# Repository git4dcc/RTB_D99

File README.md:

# RTB_D99

## This is a [opendcc](https://forum.opendcc.de/viewtopic.php?t=10443) forum project
The D99 is an advanced, open-source decoder core (AVR64DA48) designed for serious modelers. It provides individual, high-density control for up to 32 LEDs and 4 auxiliary ports. More than just control, this core is engineered for ultimate reliability:
- **Flicker-Free Power:** Includes charging logic for external Polymer or Supercapacitors for robust power backup.
- **Real-Time Diagnostics:** Harness the power of Railcom DYN to transmit vital data, including Quality of Service (QoS), track voltage, and temperature, back to your central station.
- **DIY High-Density:** Fully open-source KiCad design (4-layer PCB) ready for reflow assembly.
- **WS28xx bus**: Can drive up to 32 LEDs on a WS28xx serial bus

LED base carrier
- [Example-1: HO Roco #44741 coach](ledbase/Roco_44741)

<br>

<details>
<summary>User Guides</summary>

- User Guide - DE
- [User Guide - EN](https://rtb4dcc.de/rtb_decoder_reference_en/)

</details>

<br>

## Decoder features
- **DCC**
  - DCC-A automatic logon
  - DCC-R protocol extension
  - Service Mode Programming
- **Railcom**
  - Channel 1/2
  - POM, xPOM
  - DYN: QoS, Track-Voltage, Scap-Voltage, Temp, Ambient light
- **AUX ports**
  - 4 dimmable AUX ports (3.3V logic level)
  - AUX ports my be used for Servo
- **LED ports**
  - designed for
    - SR: 74HC595 shift registers
    - WS: WS2811 neo pixel
  - up to 32 individual LEDs using either SR or WS
- SUSI 3.3V
- 2.8V SCAP (optional, external to PCB)
- 16V Polymer Caps (optional, external to PCB)
- Inrush limited
- max track voltage 36V
- CPU heartbeat LED
- ambient light sensor (optional)
- fast firmware update on main tracks via DCC-R

# Hardware
The current PCB layout uses SMD footprints with 0.4mm pitch and mainly 0402 parts. Reflow soldering is mandatory.
The layout has been optimized to automatic PCB assembly.

| top | bottom |
| --- | --- |
|  |  |

## PCB
- 4-layer PCB, FR4, 28 x 15 x 0.8mm
- CPU: AVR64DA48

<details>
<summary>Details</summary>

<br>

<br><br>

| pin | label | direction | description |
| --- | --- | --- | --- |
| 1 | DCC-b | input | DCC signal from track |
| 3 | DCC-1 | input | DCC signal from track |
| 5 | GND | output | Decoder ground signal (after rectifier) |
| 7 | AUX-4 | output | Logic level auxiliary port (3.3V) |
| 9 | AUX-3 | output | Logic level auxiliary port (3.3V) |
| 11 | AUX-2 | output | Logic level auxiliary port (3.3V) |
| 13 | AUX-1 | output | Logic level auxiliary port (3.3V) |
| 15 | GND | output | same as pin 5 |
| 17 | VTRK | output | (+) Track voltage after rectifier (goes up to 25V) |
| 19 | NCAP | output | (+) Connect to external polymer capacitors (cap must tolerate 16V) |
| 2 | 3V3 | output | (+) Decoder CPU voltage (3.3V) |
| 4 | SUSI_clk | output | SUSI clock signal (3.3V) |
| 6 | SUSI_dat | output | SUSI data signal (3.3V) |
| 8 | uOpto | input | Connects an optional ambient light sensor |
| 10 | UPDI | in/out | CPU programming port |
| 12 | LED.oe | output | Connect to HC595 shift register output enable pin |
| 14 | LED.stcp | output | Connect to HC595 shift register staging clock pin |
| 16 | LED.ds | output | Connect to HC595 shift register data pin |
| 18 | LED.ds | output | Connect to HC595 shift register shift clock pin |
| 20 | SCAP | output | (+) Connect to external supercap (cap must tolerate 2.8V) |

</details>

## Kicad
[Schematic](doc/D99_schematic.pdf) | [Layout](doc/D99_layout.pdf) | [Gerber](gerber)

<details>
<summary>Dependency</summary>
<br>

:yellow_circle: Requires my Kicad project library [RTB_SamacSys](/../../../../git4dcc/RTB_SamacSys) in the same directory tree.

</details>

## Firmware
Filename structure: { **pcb** }{ **code** }{ **version** }.hex

Example: **D99F0001**.hex

|   | Description |
| --- | --- |
| **pcb** | Name of matching hardware (**D99**) |
| **code** | Type of code contained (**R**=rom, **B**=bootloader, **F**=flash, **U**=bld update, **P**=UPDI factory code) |
| **version** | Release version (**####**) |

[Firmware files](firmware)

## UPDI / Fuses
The fuse settings as well as the P-code (D99Pxxxx.hex) has to be installed by using UPDI.<br>

| Fuses Setting |
| --- |
||

# Images

# YouTube
See the D99 decoder core prototype in action piggyback on a LED test carrier.<br><br>

This project is intended for hobby use only and is distributed in accordance with the Apache License 2.0 agreement.

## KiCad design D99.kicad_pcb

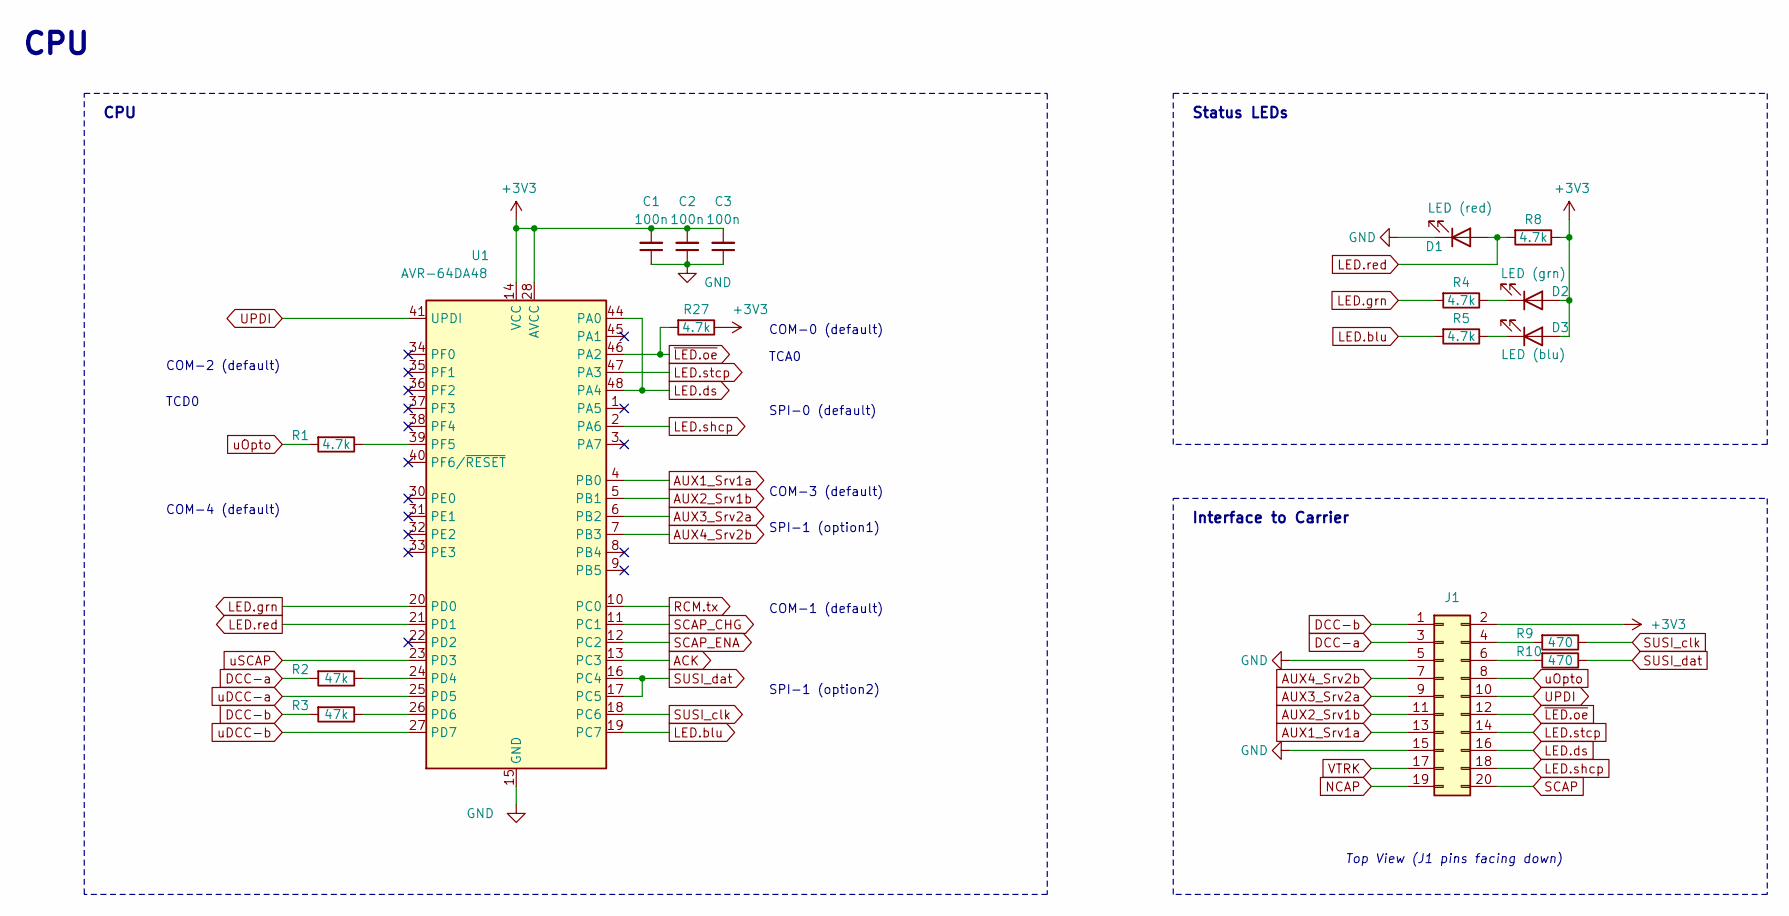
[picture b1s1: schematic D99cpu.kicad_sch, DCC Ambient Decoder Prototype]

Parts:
C1, C2, C3: 100n; C_0402_1005Metric; LCSC Part # C1525
D1: LED (red); LED_0603_1608Metric
D2: LED (grn); LED_0603_1608Metric
D3: LED (blu); LED_0603_1608Metric
J1: Conn_02x10_Counter_Clockwise; PinHeader_2x10_P1.27mm_Vertical
R1, R27: 4.7k; R_0402_1005Metric; LCSC Part # C25900
R2, R3: 47k; R_0402_1005Metric; LCSC Part # C25792
R4, R5, R8: 4.7k; R_0603_1608Metric; LCSC Part # C23162
R9, R10: 470; R_0402_1005Metric; LCSC Part # C25117
U1: AVR-64DA48; UQFN-48-1EP_6x6mm_P0.4mm_EP4.62x4.62mm; LCSC Part # C3227399

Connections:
+3V3: C1.2, C2.2, C3.2, D2.2 (A), D3.2 (A), J1.2, R8.1, R27.1, U1.14 (VCC), U1.28 (AVCC), U1.42 (VCC); also elsewhere on the board
ACK: U1.13 (PC3); also elsewhere on the board
AUX1_Srv1a: J1.13, U1.4 (PB0)
AUX2_Srv1b: J1.11, U1.5 (PB1)
AUX3_Srv2a: J1.9, U1.6 (PB2)
AUX4_Srv2b: J1.7, U1.7 (PB3)
DCC-a: J1.3, R2.2; also elsewhere on the board
DCC-b: J1.1, R3.2; also elsewhere on the board
GND: C1.1, C2.1, C3.1, D1.1 (K), J1.5, J1.15, U1.15 (GND), U1.29 (GND), U1.43 (GND), U1.49 (GND); also elsewhere on the board
LED.blu: R5.2, U1.19 (PC7)
LED.ds: J1.16, U1.44 (PA0), U1.48 (PA4)
LED.grn: R4.2, U1.20 (PD0)
LED.red: D1.2 (A), R8.2, U1.21 (PD1)
LED.shcp: J1.18, U1.2 (PA6)
LED.stcp: J1.14, U1.47 (PA3)
NCAP: J1.19; also elsewhere on the board
unnamed: D2.1 (K), R4.1
unnamed: D3.1 (K), R5.1
unnamed: J1.4, R9.2
unnamed: J1.6, R10.2
unnamed: R2.1, U1.24 (PD4)
unnamed: R3.1, U1.26 (PD6)
unnamed: R1.1, U1.39 (PF5)
RCM.tx: U1.10 (PC0); also elsewhere on the board
SCAP: J1.20, U1.23 (PD3); also elsewhere on the board
SCAP_CHG: U1.11 (PC1); also elsewhere on the board
SCAP_ENA: U1.12 (PC2); also elsewhere on the board
SUSI_clk: R9.1, U1.18 (PC6)
SUSI_dat: R10.1, U1.16 (PC4), U1.17 (PC5)
UPDI: J1.10, U1.41 (UPDI)
VTRK: J1.17; also elsewhere on the board
uDCC-a: U1.25 (PD5); also elsewhere on the board
uDCC-b: U1.27 (PD7); also elsewhere on the board
uOpto: J1.8, R1.2
~LED.oe: J1.12, R27.2, U1.46 (PA2)

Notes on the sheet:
SPI-0 (default)
TCD0
SPI-1 (option1)
Interface to Carrier
Top View (J1 pins facing down)
COM-4 (default)
CPU
COM-3 (default)
Status LEDs
SPI-1 (option2)
COM-1 (default)
COM-0 (default)
COM-2 (default)
TCA0

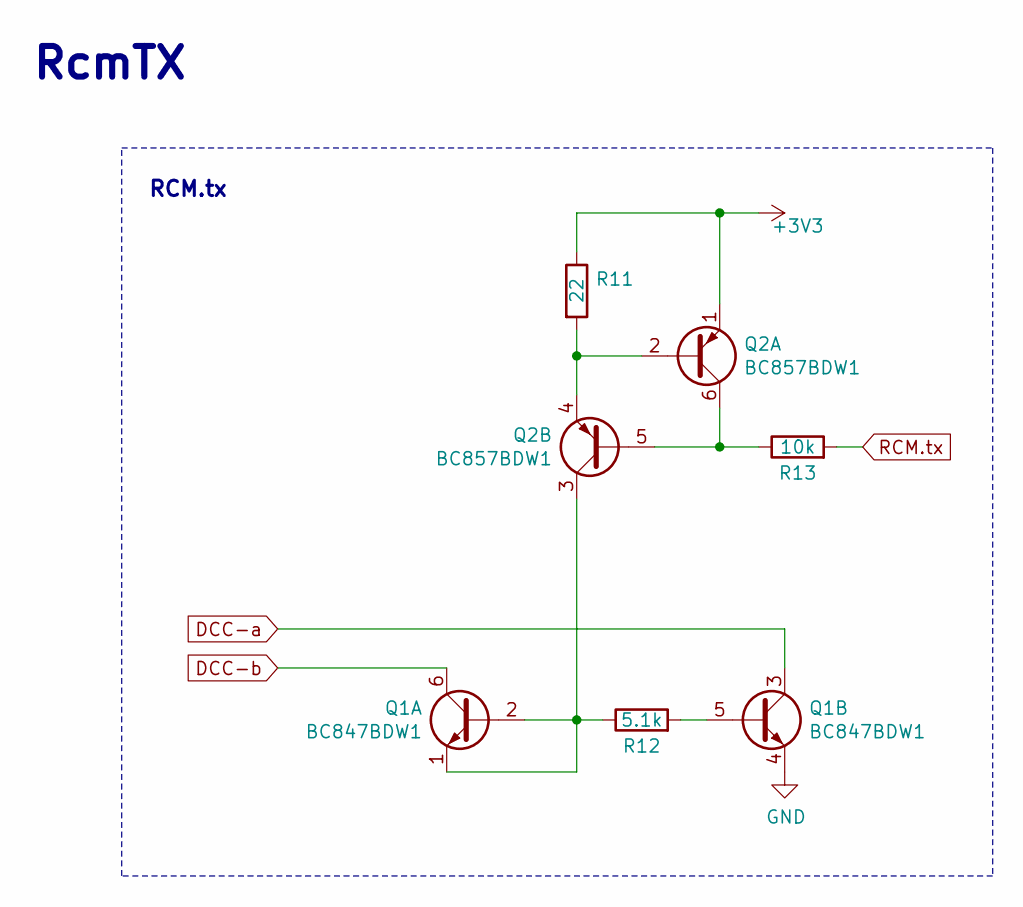
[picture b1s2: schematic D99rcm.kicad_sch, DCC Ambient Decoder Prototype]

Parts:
Q1: BC847BDW1; SOT-363_SC-70-6; LCSC Part # C82368
Q2: BC857BDW1; SOT-363_SC-70-6; LCSC Part # C154783
R11: 22; R_0402_1005Metric; LCSC Part # C25092
R12: 5.1k; R_0402_1005Metric; LCSC Part # C25905
R13: 10k; R_0402_1005Metric; LCSC Part # C25744

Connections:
+3V3: Q2.1 (E1), R11.1; also elsewhere on the board
DCC-a: Q1.3 (C2); also elsewhere on the board
DCC-b: Q1.6 (C1); also elsewhere on the board
GND: Q1.4 (E2); also elsewhere on the board
unnamed: Q1.1 (E1), Q1.2 (B1), Q2.3 (C2), R12.1
unnamed: Q1.5 (B2), R12.2
unnamed: Q2.2 (B1), Q2.4 (E2), R11.2
unnamed: Q2.5 (B2), Q2.6 (C1), R13.1
RCM.tx: R13.2; also elsewhere on the board

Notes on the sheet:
RcmTX
RCM.tx

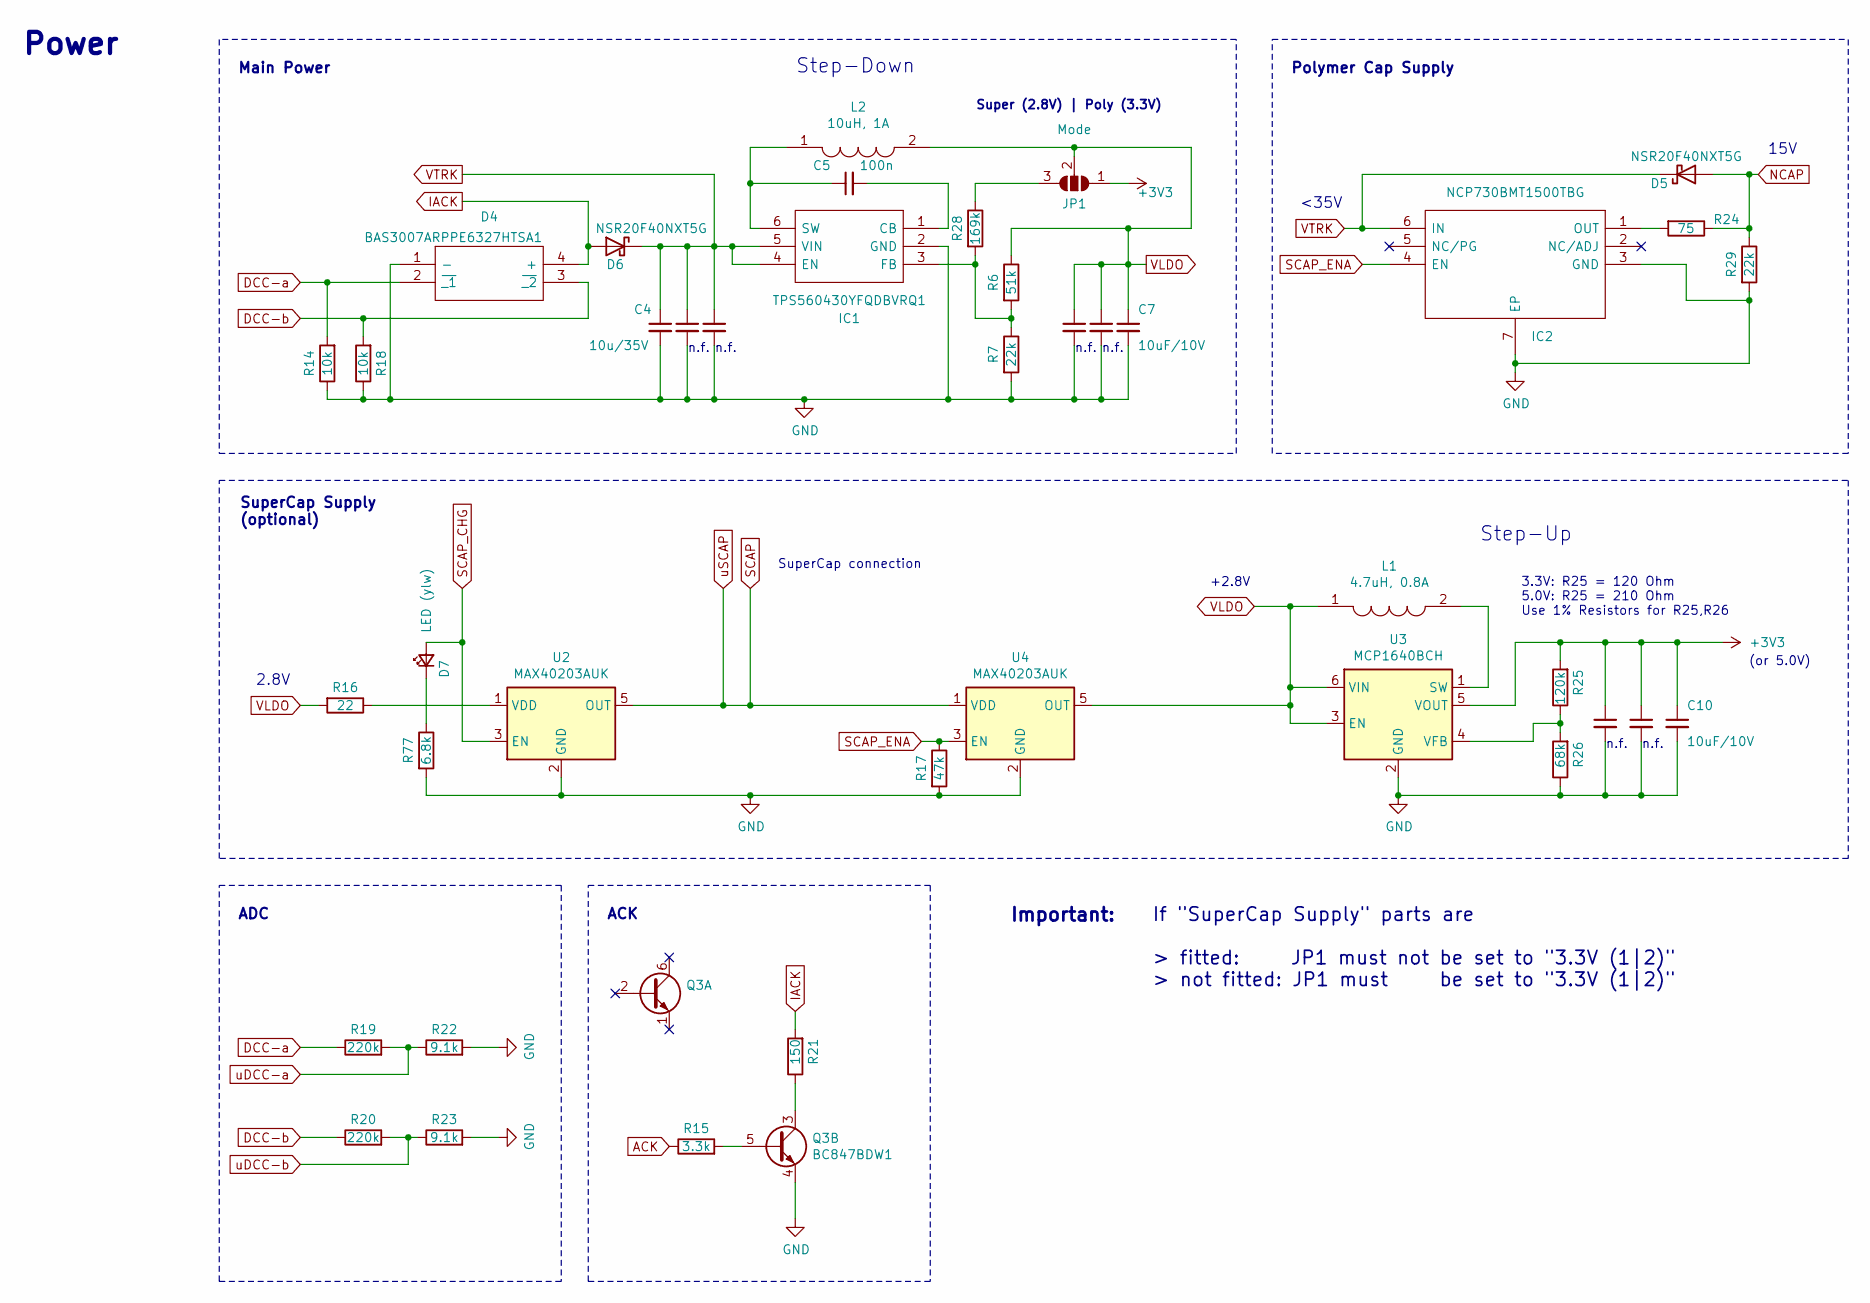
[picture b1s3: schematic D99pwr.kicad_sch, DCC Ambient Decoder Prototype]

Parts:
C4, C12, C13: 10u/35V; C_0603_1608Metric; LCSC Part # C194427
C5: 100n; C_0402_1005Metric; LCSC Part # C307331
C6, C7, C8, C9, C10, C11: 10uF/10V; C_0603_1608Metric; LCSC Part # C19702
D4: BAS3007ARPPE6327HTSA1; BF998215; LCSC Part # C6430958
D5, D6: NSR20F40NXT5G; LCSC Part # C153761
D7: LED (ylw); LED_0603_1608Metric
IC1: TPS560430YFQDBVRQ1; SOT95P280X145-6N; LCSC Part # C1849549
IC2: NCP730BMT1500TBG; SON65P200X200X80-7N; LCSC Part # C892817
JP1: Mode; SolderJumper-3_P1.3mm_Open_Pad1.0x1.5mm
L1: 4.7uH, 0.8A; WE-TPC_282892; LCSC Part # C2649333
L2: 10uH, 1A; WE-TPC_282892; LCSC Part # C2045611
Q3: BC847BDW1; SOT-363_SC-70-6; LCSC Part # C82368
R6: 51k; R_0402_1005Metric; LCSC Part # C25794
R7, R29: 22k; R_0402_1005Metric; LCSC Part # C25768
R14, R18: 10k; R_0402_1005Metric; LCSC Part # C25744
R15: 3.3k; R_0402_1005Metric; LCSC Part # C25890
R16: 22; R_0402_1005Metric; LCSC Part # C25092
R17: 47k; R_0402_1005Metric; LCSC Part # C25792
R19, R20: 220k; R_0402_1005Metric; LCSC Part # C25767
R21: 150; R_0603_1608Metric; LCSC Part # C22808
R22, R23: 9.1k; R_0402_1005Metric; LCSC Part # C25926
R24: 75; R_0603_1608Metric; LCSC Part # C4275
R25: 120k; R_0402_1005Metric; LCSC Part # C25750
R26: 68k; R_0402_1005Metric; LCSC Part # C36871
R28: 169k; R_0402_1005Metric; LCSC Part # C25758
R77: 6.8k; R_0603_1608Metric; LCSC Part # C23212
U2, U4: MAX40203AUK; SOT-23-5; LCSC Part # C2653639
U3: MCP1640BCH; SOT-23-6; LCSC Part # C478087

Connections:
+3V3: C8.1, C10.1, C11.1, JP1.1 (A), R25.2, U3.5 (VOUT); also elsewhere on the board
ACK: R15.1; also elsewhere on the board
DCC-a: D4.2 (~_1), R14.2, R19.1; also elsewhere on the board
DCC-b: D4.3 (~_2), R18.2, R20.1; also elsewhere on the board
GND: C4.2, C6.2, C7.2, C8.2, C9.2, C10.2, C11.2, C12.2, C13.2, D4.1 (-), IC1.2 (GND), IC2.3 (GND), IC2.7 (EP), Q3.4 (E2), R7.2, R14.1, R17.2, R18.1, R22.2, R23.2, R26.1, R29.2, R77.2, U2.2 (GND), U3.2 (GND), U4.2 (GND); also elsewhere on the board
IACK: D4.4 (+), D6.2 (A), R21.2
NCAP: D5.2 (A), R24.1, R29.1; also elsewhere on the board
unnamed: D7.1 (K), R77.1
unnamed: C5.2, IC1.1 (CB)
unnamed: IC1.3 (FB), R6.2, R7.1, R28.2
unnamed: C5.1, IC1.6 (SW), L2.1
unnamed: IC2.1 (OUT), R24.2
unnamed: JP1.3 (B), R28.1
unnamed: Q3.5 (B2), R15.2
unnamed: Q3.3 (C2), R21.1
unnamed: R16.1, U2.1 (VDD)
unnamed: L1.2, U3.1 (SW)
unnamed: R25.1, R26.2, U3.4 (VFB)
SCAP: U2.5 (OUT), U4.1 (VDD); also elsewhere on the board
SCAP_CHG: D7.2 (A), U2.3 (EN); also elsewhere on the board
SCAP_ENA: IC2.4 (EN), R17.1, U4.3 (EN); also elsewhere on the board
VLDO: C6.1, C7.1, C9.1, JP1.2 (C), L1.1, L2.2, R6.1, R16.2, U3.3 (EN), U3.6 (VIN), U4.5 (OUT)
VTRK: C4.1, C12.1, C13.1, D5.1 (K), D6.1 (K), IC1.4 (EN), IC1.5 (VIN), IC2.6 (IN); also elsewhere on the board
uDCC-a: R19.2, R22.1; also elsewhere on the board
uDCC-b: R20.2, R23.1; also elsewhere on the board

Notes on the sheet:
Step-Up
n.f.
Polymer Cap Supply
+2.8V
Super (2.8V) | Poly (3.3V)
(or 5.0V)
ACK
Step-Down
Power
<35V
3.3V: R25 = 120 Ohm 5.0V: R25 = 210 Ohm Use 1% Resistors for R25,R26
Main Power
SuperCap connection
If "SuperCap Supply" parts are > fitted: JP1 must not be set to "3.3V (1|2)" > not fitted: JP1 must be set to "3.3V (1|2)"
SuperCap Supply (optional)
2.8V
ADC
Important:
15V

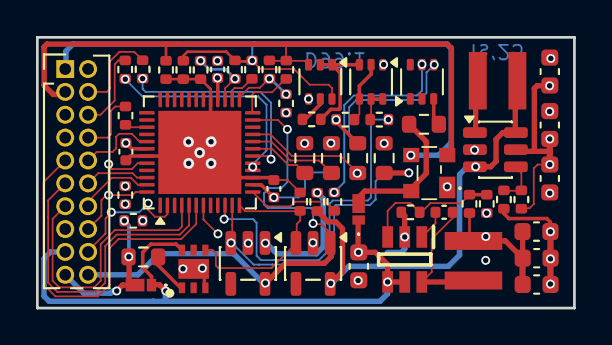
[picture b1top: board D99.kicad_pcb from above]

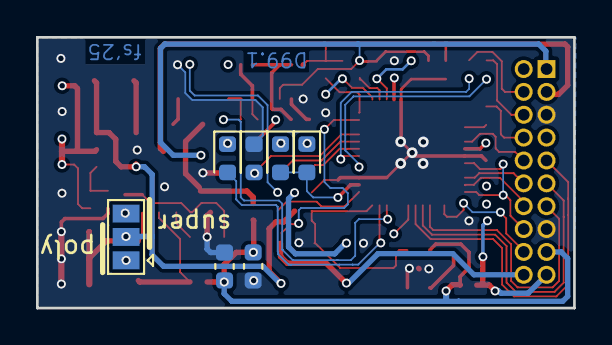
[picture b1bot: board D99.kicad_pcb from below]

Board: 4 copper layers, 29.8 x 15.0 mm, 63 parts (7 on the bottom side), 52 nets.

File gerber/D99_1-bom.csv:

Designator,Footprint,Quantity,Value,LCSC Part #
"C1, C2, C3",0402,3,100n,C1525
"C10, C11, C6, C7, C8, C9",0603,6,10uF/10V,C19702
"C12, C13, C4",0603,3,10u/35V,C194427
C5,0402,1,100n,C307331
D1,0603,1,LED (red),
D2,0603,1,LED (grn),
D3,0603,1,LED (blu),
D4,BF998215,1,BAS3007ARPPE6327HTSA1,C6430958
"D5, D6",NSR20F40NXT5G,2,NSR20F40NXT5G,C153761
D7,0603,1,LED (ylw),
IC1,SOT95P280X145-6N,1,TPS560430YFQDBVRQ1,C1849549
IC2,SON65P200X200X80-7N,1,NCP730BMT1500TBG,C892817
J1,PinHeader_2x10_P1.27mm_Vertical,1,Conn_02x10_Counter_Clockwise,
JP1,SolderJumper-3_P1.3mm_Open_Pad1.0x1.5mm,1,Mode,
L1,WE-TPC_282892,1,"4.7uH, 0.8A",C2649333
L2,WE-TPC_282892,1,"10uH, 1A",C2045611
"Q1, Q3",SOT-363_SC-70-6,2,BC847BDW1,C82368
Q2,SOT-363_SC-70-6,1,BC857BDW1,C154783
"R1, R27",0402,2,4.7k,C25900
"R10, R9",0402,2,470,C25117
"R11, R16",0402,2,22,C25092
R12,0402,1,5.1k,C25905
"R13, R14, R18",0402,3,10k,C25744
R15,0402,1,3.3k,C25890
"R17, R2, R3",0402,3,47k,C25792
"R19, R20",0402,2,220k,C25767
R21,0603,1,200,C8218
"R22, R23",0402,2,9.1k,C25926
R24,0603,1,75,C4275
R25,0402,1,120k,C25750
R26,0402,1,68k,C36871
R28,0402,1,169k,C25758
"R29, R7",0402,2,22k,C25768
"R4, R5, R8",0603,3,4.7k,C23162
R6,0402,1,51k,C25794
R77,0603,1,6.8k,C23212
U1,UQFN-48-1EP_6x6mm_P0.4mm_EP4.62x4.62mm,1,AVR-64DA48,C3227399
"U2, U4",SOT-23-5,2,MAX40203AUK,C2653639
U3,SOT-23-6,1,MCP1640BCH,C478087

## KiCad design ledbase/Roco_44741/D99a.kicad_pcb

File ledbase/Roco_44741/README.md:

# LEDbase: Roco #44741

LED base carier for H0 Roco #44741 to be used with RTB_D99.
PCB contains LEDs for ilse, cabin and lavatory. In addition, external tail light LEDs can be attached on each end.

<br>

> [!CAUTION]
> This project is **work in progress** and there may be (hope not) changes to the overall design if the current turns out to be not practical.

<br>

<br>

## LED base features
- **LED ports**
  - 4x 74HC595 shift register
  - 31 individual LEDs
- SUSI 3.3V
- 2.8V SCAP (optional)
- 16V Polymer Caps (optional)
- ambient light sensor (optional)

# Hardware
The current PCB layout uses SMD footprints. Reflow soldering is recommended.

## PCB
- 2-layer PCB, FR4, 1mm
- CPU: none

<details>
<summary>Details</summary>

## Kicad
[Schematic](doc/D99a_schematic.pdf) | [Layout](doc/D99a_layout.pdf) | [Gerber](gerber)

:yellow_circle: Requires my Kicad project library [RTB_SamacSys](https://github.com/git4dcc/RTB_SamacSys) in the same directory tree.

</details>

# Images

This project is intended for hobby use only and is distributed in accordance with the Apache License 2.0 agreement.

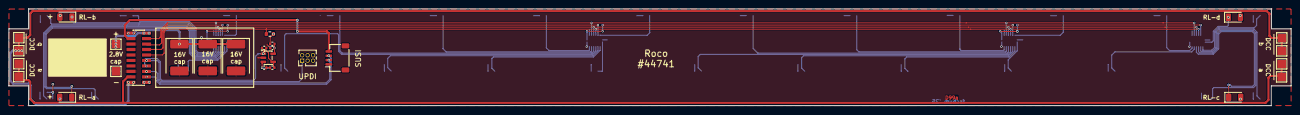
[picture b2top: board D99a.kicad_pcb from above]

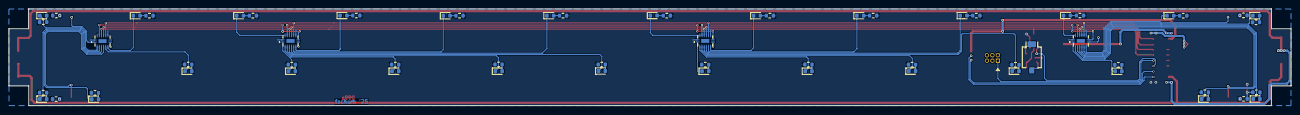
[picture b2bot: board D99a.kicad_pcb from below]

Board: 2 copper layers, 297.7 x 22.4 mm, 90 parts (63 on the bottom side), 83 nets.

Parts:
C1: 1u; C_0402_1005Metric
C3, C4, C6: 470u/16V; CP_EIA-7360-38_Kemet-E
D1, D2, D4, D5, D7, D8, D9, D10, D11, D12, D13, D14, D15, D16, D17, D18, D19, D20, D21, D22, D23, D24, D27, D29, D30, D31, D32: LED; LED_0603_1608Metric
D3, D6, D26, D28: LED; LED_1206_3216Metric
D33: SFH2440; Osram_SFH2440
J1, J2, J3, J4, J6, J7, J8, J9, J10, J11: Conn_01x01; TestPoint_Pad_2.0x2.0mm
J5: Conn_02x10_Odd_Even; PinSocket_2x10_P1.27mm_Vertical_SMD
J12: Conn_01x04; JST_SH_SM04B-SRSS-TB_1x04-1MP_P1.00mm_Horizontal
J13: Conn_01x06; PinHeader_2x03_P1.27mm_Vertical
R1: 100k; R_0603_1608Metric
R2, R3, R4, R5, R6, R7, R8, R9, R10, R11, R12, R13, R14, R15, R16, R17, R18, R19, R20, R21, R22, R23, R24, R25, R27, R28, R29, R30, R31, R32, R33: 1k; R_0603_1608Metric
R34: 120; R_0402_1005Metric
R35, R37: 330k; R_0402_1005Metric
R36: 22k; R_0402_1005Metric
U1, U2, U3, U4: 74HC595; 74HC595BQ115
U5: MCP6001x-LT; SOT-23-5

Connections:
+3.3V: J5.2, J13.2, R1.1, R2.1, R3.1, R4.1, R5.1, R6.1, R7.1, R8.1, R9.1, R10.1, R11.1, R12.1, R13.1, R14.1, R15.1, R16.1, R17.1, R18.1, R19.1, R20.1, R21.1, R22.1, R23.1, R24.1, R25.1, R27.1, R28.1, R29.1, R30.1, R31.1, R32.1, R33.1, R34.2, U1.10 (~SRCLR), U1.16 (VCC), U2.10 (~SRCLR), U2.16 (VCC), U3.10 (~SRCLR), U3.16 (VCC), U4.10 (~SRCLR), U4.16 (VCC)
DCC-a: J4.1, J5.3, J7.1, J9.1, J11.1
DCC-b: J3.1, J5.1, J6.1, J8.1, J10.1
GND: C1.2, C3.2, C4.2, C6.2, J2.1, J5.5, J5.15, J12.1, J13.6, R35.1, R36.1, U1.8 (GND), U2.8 (GND), U3.8 (GND), U4.8 (GND), U5.2 (V-)
LED.ds: J5.16, U1.14 (SER)
LED.ds1: U1.9 (QH'), U3.14 (SER)
LED.ds2: U2.14 (SER), U3.9 (QH')
LED.ds3: U2.9 (QH'), U4.14 (SER)
LED.shcp: J5.18, U1.11 (SRCLK), U2.11 (SRCLK), U3.11 (SRCLK), U4.11 (SRCLK)
LED.stcp: J5.14, U1.12 (RCLK), U2.12 (RCLK), U3.12 (RCLK), U4.12 (RCLK)
NCAP: C3.1, C4.1, C6.1, J5.19
unnamed: D1.2 (A), R2.2
unnamed: D1.1 (K), U1.15 (QA)
unnamed: D2.2 (A), R3.2
unnamed: D2.1 (K), U1.1 (QB)
unnamed: D3.2 (A), R4.2
unnamed: D3.1 (K), U1.2 (QC)
unnamed: D4.2 (A), R5.2
unnamed: D4.1 (K), U1.3 (QD)
unnamed: D5.2 (A), R6.2
unnamed: D5.1 (K), U1.4 (QE)
unnamed: D6.2 (A), R8.2
unnamed: D6.1 (K), U1.6 (QG)
unnamed: D7.2 (A), R7.2
unnamed: D7.1 (K), U1.5 (QF)
unnamed: D8.2 (A), R9.2
unnamed: D8.1 (K), U1.7 (QH)
unnamed: D9.2 (A), R10.2
unnamed: D9.1 (K), U2.15 (QA)
unnamed: D10.2 (A), R11.2
unnamed: D10.1 (K), U2.1 (QB)
unnamed: D11.2 (A), R12.2
unnamed: D11.1 (K), U2.2 (QC)
unnamed: D12.2 (A), R13.2
unnamed: D12.1 (K), U2.3 (QD)
unnamed: D13.2 (A), R14.2
unnamed: D13.1 (K), U2.4 (QE)
unnamed: D14.2 (A), R15.2
unnamed: D14.1 (K), U2.5 (QF)
unnamed: D15.2 (A), R16.2
unnamed: D15.1 (K), U2.6 (QG)
unnamed: D16.2 (A), R17.2
unnamed: D16.1 (K), U2.7 (QH)
unnamed: D17.2 (A), R18.2
unnamed: D17.1 (K), U3.15 (QA)
unnamed: D18.2 (A), R19.2
unnamed: D18.1 (K), U3.1 (QB)
unnamed: D19.2 (A), R20.2
unnamed: D19.1 (K), U3.2 (QC)
unnamed: D20.2 (A), R21.2
unnamed: D20.1 (K), U3.3 (QD)
unnamed: D21.2 (A), R22.2
unnamed: D21.1 (K), U3.4 (QE)
unnamed: D22.2 (A), R23.2
unnamed: D22.1 (K), U3.5 (QF)
unnamed: D23.2 (A), R24.2
unnamed: D23.1 (K), U3.6 (QG)
unnamed: D24.2 (A), R25.2
unnamed: D24.1 (K), U3.7 (QH)
unnamed: D26.2 (A), R27.2
unnamed: D26.1 (K), U4.1 (QB)
unnamed: D27.2 (A), R28.2
unnamed: D27.1 (K), U4.2 (QC)
unnamed: D28.2 (A), R31.2
unnamed: D28.1 (K), U4.5 (QF)
unnamed: D29.2 (A), R29.2
unnamed: D29.1 (K), U4.3 (QD)
unnamed: D30.2 (A), R30.2
unnamed: D30.1 (K), U4.4 (QE)
unnamed: D31.2 (A), R32.2
unnamed: D31.1 (K), U4.6 (QG)
unnamed: D32.2 (A), R33.2
unnamed: D32.1 (K), U4.7 (QH)
unnamed: D33.2 (A), R35.2, U5.3 (+)
unnamed: C1.1, D33.1 (K), R34.1, U5.5 (V+)
unnamed: R36.2, R37.2, U5.4 (-)
SCAP: J1.1, J5.20
SUSI_clk: J5.4, J12.3
SUSI_dat: J5.6, J12.2
UPDI: J5.10, J13.1
VTRK: J5.17, J12.4
uOpto: J5.8, R37.1, U5.1
~LED.oe: J5.12, R1.2, U1.13 (~OE), U2.13 (~OE), U3.13 (~OE), U4.13 (~OE)

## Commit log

2025-10-14 initial
2025-10-19 add: ledbase Roco_44741
2025-10-19 Add LED base section to README
    Added LED base section with reference to Roco #44741.
2025-10-19 Add optional ambient light sensor to README
    Added information about the ambient light sensor as an optional feature.
2025-11-05 mod: ncap leakage resistor
2025-11-05 Update README with more images
    Added additional images to the README for better illustration.
2025-11-15 mod: refactoring
2025-11-18 mod: CV642 options
2025-11-18 Remove details section for UPDI / Fuses
    Removed details section for fuse settings in README.
2025-11-21 fix: CV642 handling
2026-01-19 fix: R25 had incorrect footnote
2026-02-20 Update link to RTB_SamacSys library in README
2026-02-20 git mirror test
2026-02-22 Revise README with new project details and badges
    Updated project description and badge links in README.md.
